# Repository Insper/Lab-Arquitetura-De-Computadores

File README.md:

# Lab-Arquitetura-De-Computadores
Materiais do laboratório de Arquitetura De Computadores Do Insper - Sistemas Embarcados!

## Equipamentos

- Analisador lógico
  - 1x Saleae Logic Pro 16
  - 12x Saleae Logic 8  
- Osciloscópio
  - 3x Tektronix DPO2012B
- Gerador de Sinais
  - 3x Tektronix AFG3021
- Multímetro de Bancada
  - 3x Tektronix DMM4040
- Fonte configurável
  - 6x Tektronix PWS4343

## Kits de desenvolvimento

- microcontrolador
  - 55x SAE70-XPLD
- FPGA SOC
  - 6x DE0-CV
  - 12x Hélio
- FPGA
  - DE5a-NET-DDR4

## Módulos

Os seguinte módulos estão disponíveis no laboratório:

### Atuadores

### Sensores

### Comunicacao

### Interface

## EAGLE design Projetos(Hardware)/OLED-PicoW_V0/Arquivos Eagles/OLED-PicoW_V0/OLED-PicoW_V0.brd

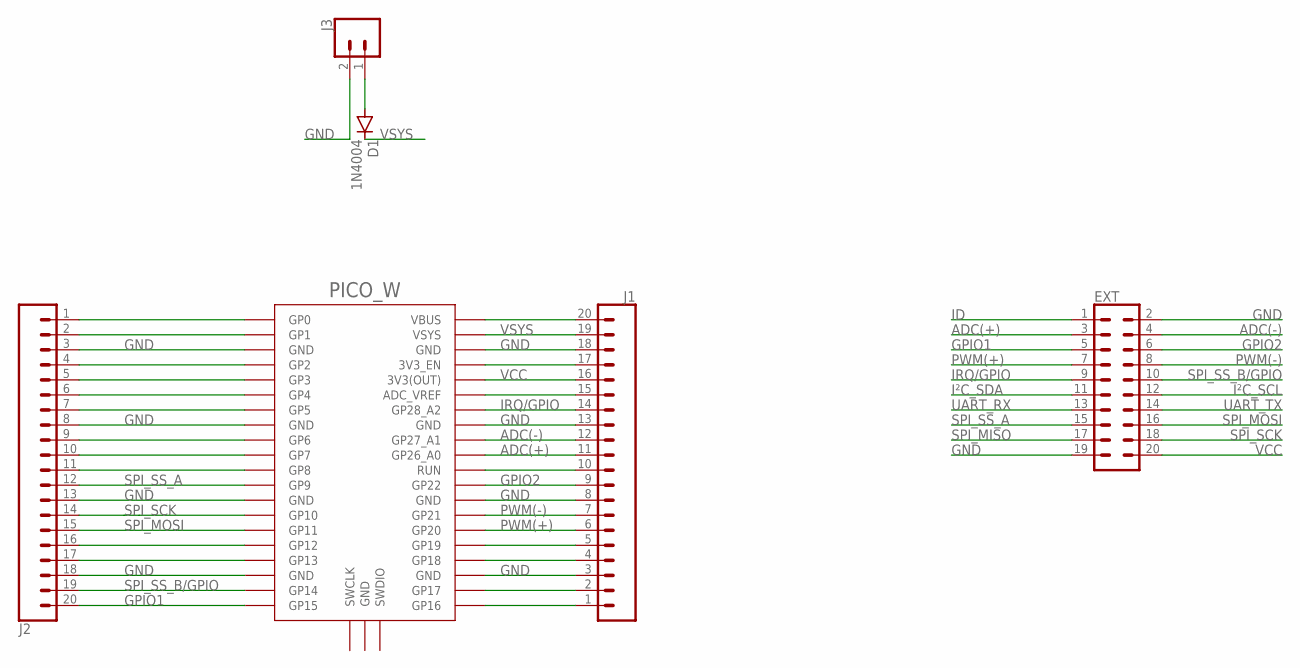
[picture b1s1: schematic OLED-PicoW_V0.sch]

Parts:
D1: 1N4004; DO41-10
EXT: CONN_10X2; 2X10
J1, J2: CONN_20; 1X20
J3: CONN_023.5MM; SCREWTERMINAL-3.5MM-2
PICO_W: RPI_PICO_IG-TH; RPI_PICO_TH

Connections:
ADC(+): EXT.3, J1.11, PICO_W.GP26_A0
ADC(-): EXT.4, J1.12, PICO_W.GP27_A1
GND: EXT.2, EXT.19, J1.3, J1.8, J1.13, J1.18, J2.3, J2.8, J2.13, J2.18, J3.2, PICO_W.AGND (GND), PICO_W.GND@1 (GND), PICO_W.GND@2 (GND), PICO_W.GND@3 (GND), PICO_W.GND@4 (GND), PICO_W.GND@6 (GND), PICO_W.GND@7 (GND), PICO_W.GND@8 (GND)
GPIO1: EXT.5, J2.20, PICO_W.GP15
GPIO2: EXT.6, J1.9, PICO_W.GP22
ID: EXT.1
IRQ/GPIO: EXT.9, J1.14, PICO_W.GP28_A2
I²C_SCL: EXT.12
I²C_SDA: EXT.11
unnamed: J1.20, PICO_W.VBUS
unnamed: J1.5, PICO_W.GP19
unnamed: J1.17, PICO_W.3V3_EN
unnamed: J1.15, PICO_W.ADC_VREF
unnamed: J1.4, PICO_W.GP18
unnamed: J1.10, PICO_W.RUN
unnamed: J1.2, PICO_W.GP17
unnamed: J1.1, PICO_W.GP16
unnamed: J2.1, PICO_W.GP0
unnamed: J2.2, PICO_W.GP1
unnamed: J2.4, PICO_W.GP2
unnamed: J2.5, PICO_W.GP3
unnamed: J2.6, PICO_W.GP4
unnamed: J2.7, PICO_W.GP5
unnamed: J2.9, PICO_W.GP6
unnamed: J2.10, PICO_W.GP7
unnamed: J2.11, PICO_W.GP8
unnamed: J2.16, PICO_W.GP12
unnamed: J2.17, PICO_W.GP13
unnamed: D1.A, J3.1
PWM(+): EXT.7, J1.6, PICO_W.GP20
PWM(-): EXT.8, J1.7, PICO_W.GP21
SPI_MISO: EXT.17
SPI_MOSI: EXT.16, J2.15, PICO_W.GP11
SPI_SCK: EXT.18, J2.14, PICO_W.GP10
SPI_SS_A: EXT.15, J2.12, PICO_W.GP9
SPI_SS_B/GPIO: EXT.10, J2.19, PICO_W.GP14
UART_RX: EXT.13
UART_TX: EXT.14
VCC: EXT.20, J1.16, PICO_W.3V3(OUT)
VSYS: D1.C, J1.19, PICO_W.VSYS

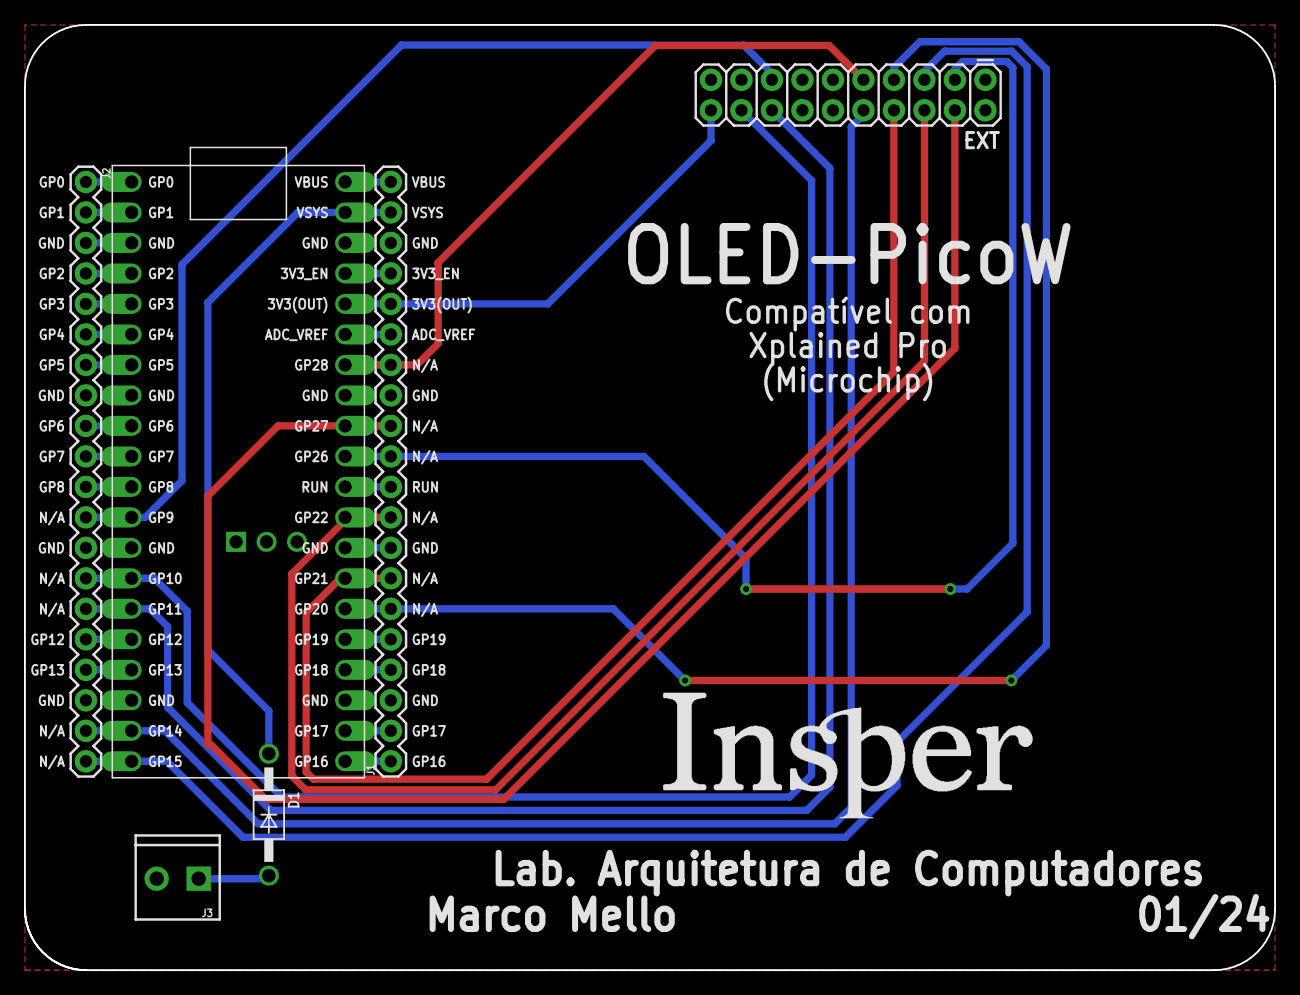
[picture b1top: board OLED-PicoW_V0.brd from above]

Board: 2 copper layers, 104.1 x 78.7 mm, 6 parts (0 on the bottom side), 34 nets.

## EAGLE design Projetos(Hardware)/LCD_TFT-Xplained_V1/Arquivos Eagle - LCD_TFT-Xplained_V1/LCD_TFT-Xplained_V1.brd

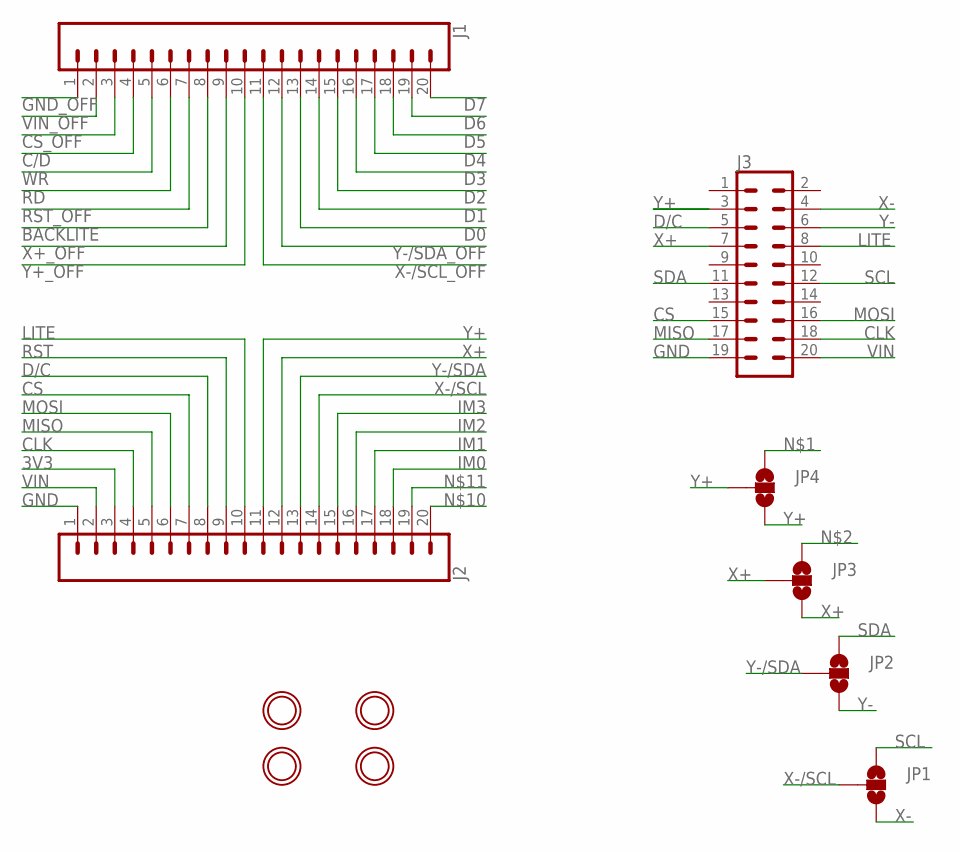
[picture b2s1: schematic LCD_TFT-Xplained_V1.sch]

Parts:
J1, J2: CONN_20NOSILK; 1X20_NOSILK
J3: CONN_10X2; 2X10
JP1, JP2, JP3, JP4: JUMPER-SMT_3_NO_NO-SILK; SMT-JUMPER_3_NO_NO-SILK
U$1, U$2, U$3, U$4: MOUNTINGHOLE3.0THIN; MOUNTINGHOLE_3.0_PLATEDTHIN

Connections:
3V3: J2.3
BACKLITE: J1.8
C/D: J1.4
CLK: J2.4, J3.18
CS: J2.7, J3.15
CS_OFF: J1.3
D0: J1.13
D1: J1.14
D2: J1.15
D3: J1.16
D4: J1.17
D5: J1.18
D6: J1.19
D7: J1.20
D/C: J2.8, J3.5
GND: J2.1, J3.19
GND_OFF: J1.1
IM0: J2.18
IM1: J2.17
IM2: J2.16
IM3: J2.15
LITE: J2.10, J3.8
MISO: J2.5, J3.17
MOSI: J2.6, J3.16
RD: J1.6
RST: J2.9
RST_OFF: J1.7
SCL: J3.12, JP1.1
SDA: J3.11, JP2.1
VIN: J2.2, J3.20
VIN_OFF: J1.2
WR: J1.5
X+: J2.12, J3.7, JP3.2, JP3.3
X+_OFF: J1.9
X-: J3.4, JP1.3
X-/SCL: J2.14, JP1.2
X-/SCL_OFF: J1.11
Y+: J2.11, J3.3, JP4.2, JP4.3
Y+_OFF: J1.10
Y-: J3.6, JP2.3
Y-/SDA: J2.13, JP2.2
Y-/SDA_OFF: J1.12

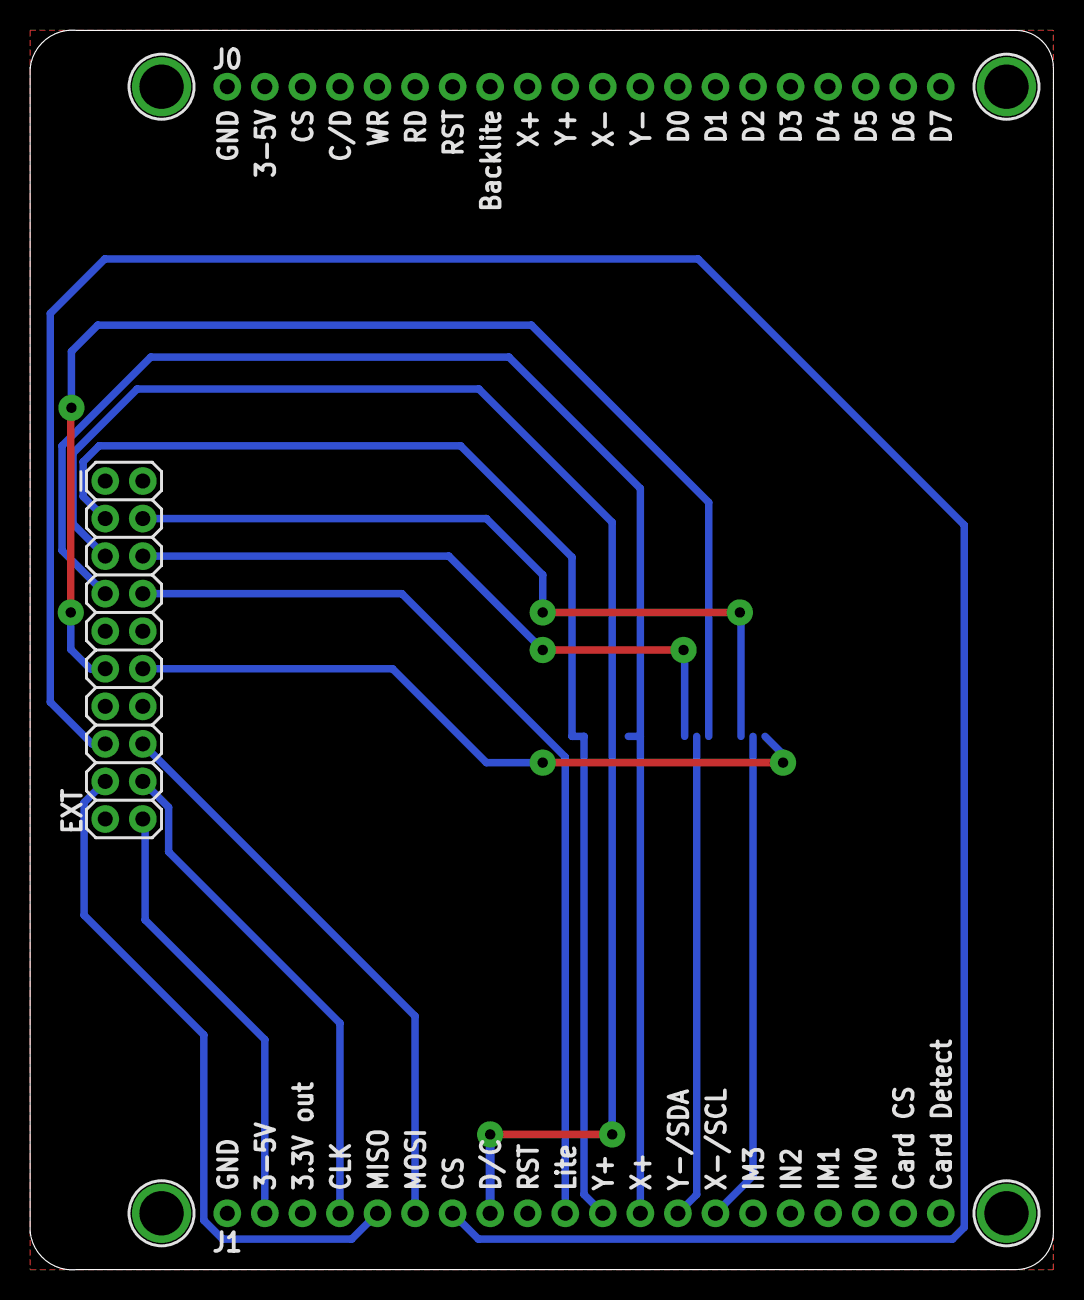
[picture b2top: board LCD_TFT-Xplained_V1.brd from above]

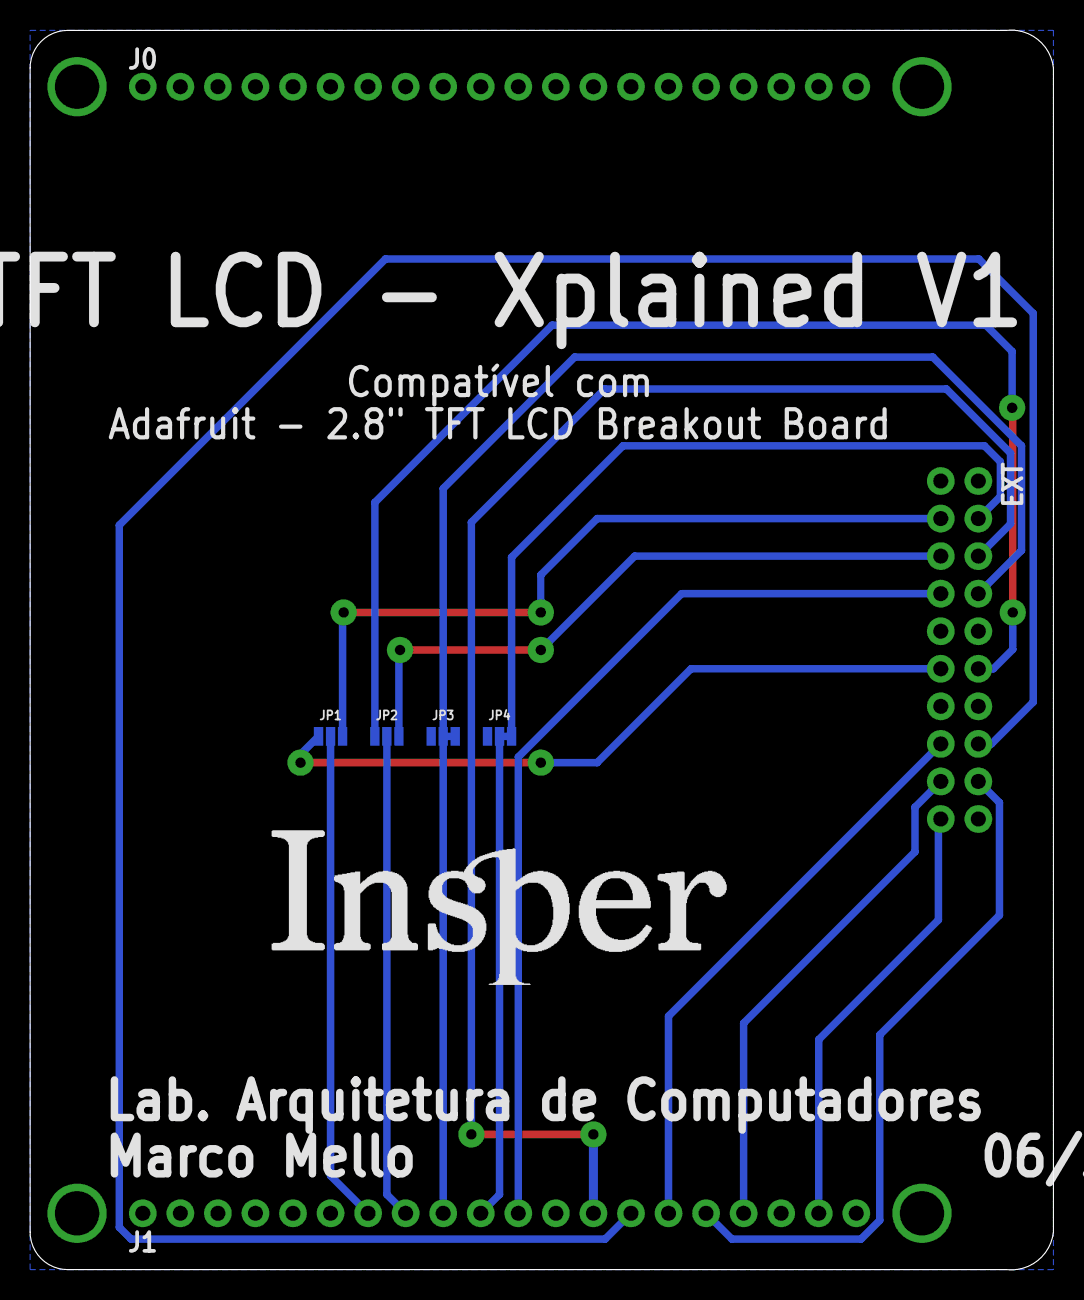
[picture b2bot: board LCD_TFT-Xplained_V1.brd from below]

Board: 2 copper layers, 69.2 x 83.9 mm, 11 parts (4 on the bottom side), 16 nets.

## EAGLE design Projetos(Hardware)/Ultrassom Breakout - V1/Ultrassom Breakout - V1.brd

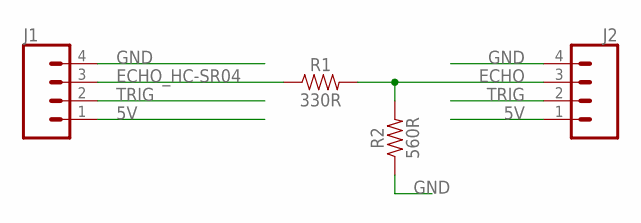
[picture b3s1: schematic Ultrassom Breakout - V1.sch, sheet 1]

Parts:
J1, J2: CONN_041X04_NO_SILK; 1X04_NO_SILK
R1: 330R; AXIAL-0.3-KIT
R2: 560R; AXIAL-0.3-KIT

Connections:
5V: J1.1, J2.1
ECHO: J2.3, R1.P$2 (2), R2.P$2 (2)
ECHO_HC-SR04: J1.3, R1.P$1 (1)
GND: J1.4, J2.4, R2.P$1 (1)
TRIG: J1.2, J2.2

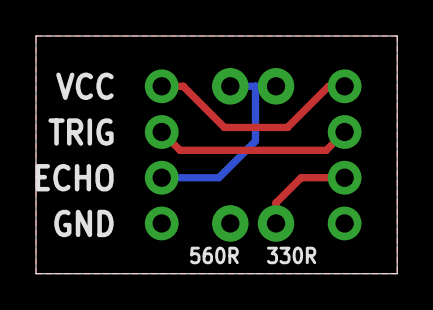
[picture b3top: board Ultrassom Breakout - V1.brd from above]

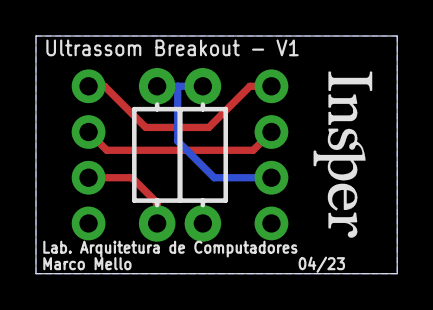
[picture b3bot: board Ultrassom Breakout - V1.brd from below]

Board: 2 copper layers, 20.1 x 13.2 mm, 4 parts (4 on the bottom side), 5 nets.

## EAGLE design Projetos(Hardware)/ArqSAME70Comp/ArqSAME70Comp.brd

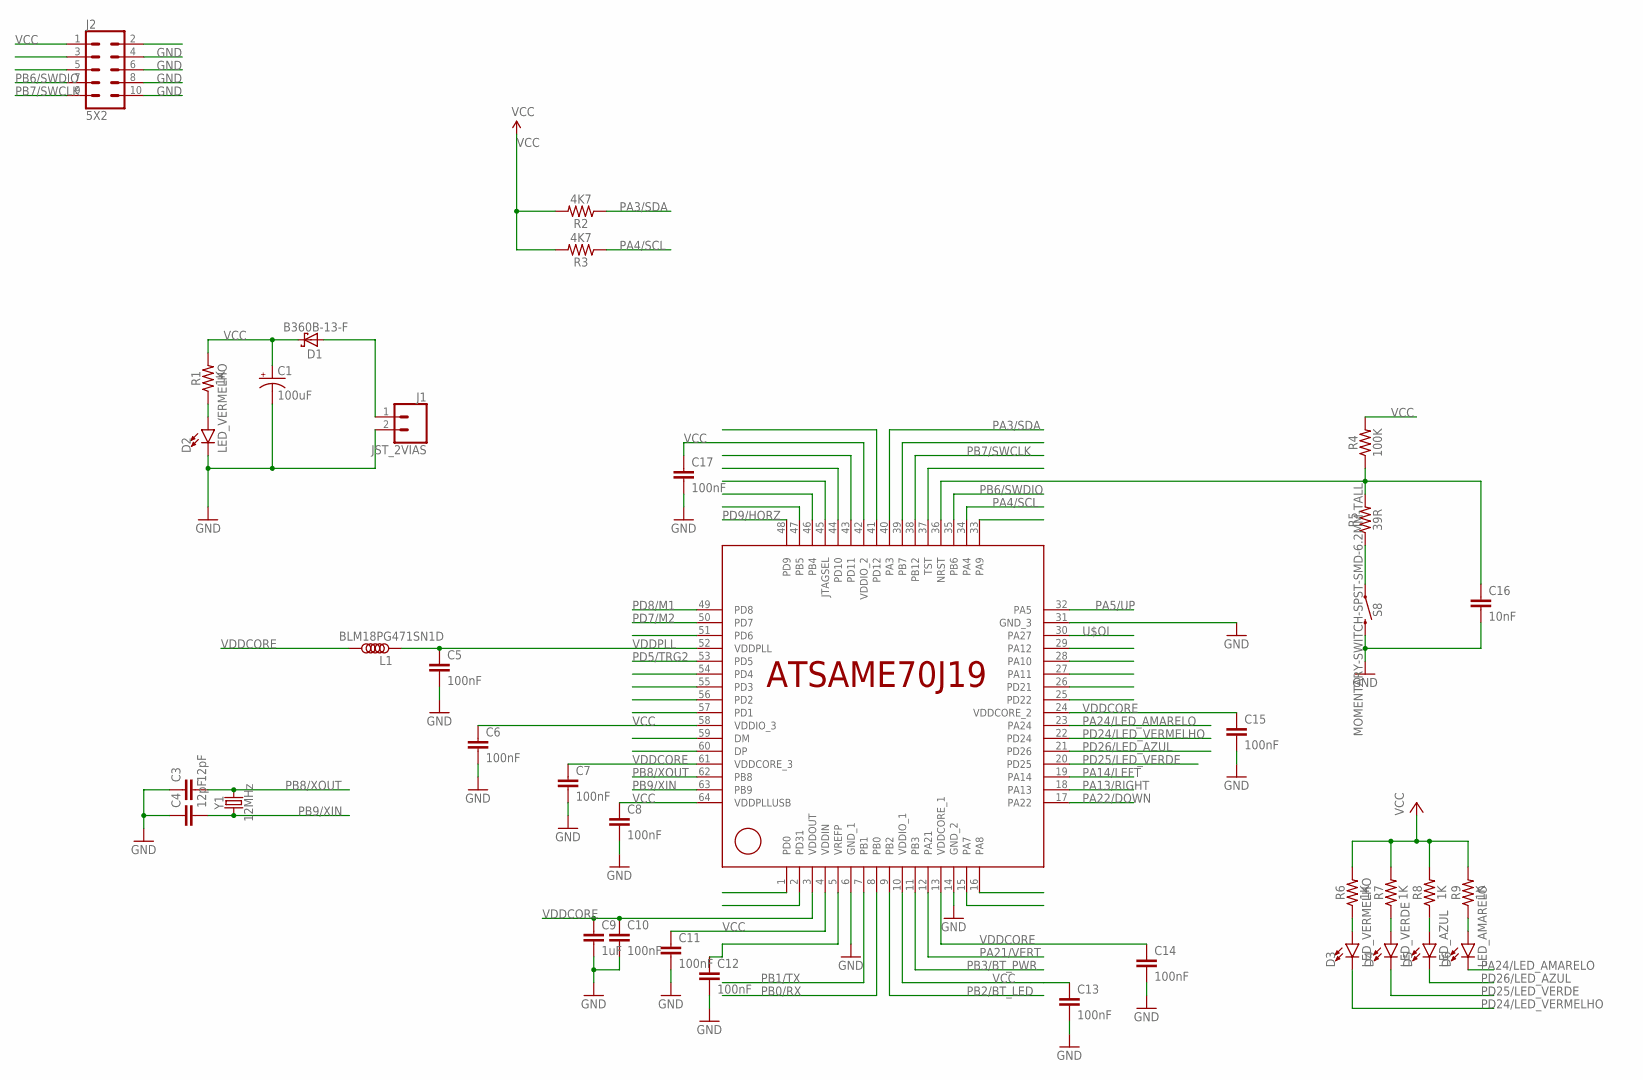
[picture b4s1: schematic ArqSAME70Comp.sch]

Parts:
C1: 100uF; PANASONIC_D
C3, C4: 12pF; 0603
C5, C6, C7, C8, C10, C11, C12, C13, C14, C15, C17: 100nF; C0603K
C9: 1uF; C0603K
C16: 10nF; C0603K
D1: B360B-13-F; DIODE_SMB
D2, D3: LED_VERMELHO; LED-1206
D4: LED_VERDE; LED-1206
D5: LED_AZUL; LED-1206
D6: LED_AMARELO; LED-1206
J1: JST_2VIAS; JST-2-SMD
J2: 5X2; 2X5
L1: BLM18PG471SN1D; PACKAGE_0603
R1, R6, R7, R8, R9: 1K; R0603
R2, R3: 4K7; R0603
R4: 100K; R0603
R5: 39R; R0603
S8: MOMENTARY-SWITCH-SPST-SMD-6.2MM-TALL; TACTILE_SWITCH_SMD_6.2MM_TALL
UC: ATSAME70J19_LQFP64; LQFP64
Y1: 12MHz; CRYSTAL-SMD-5X3.2-4PAD

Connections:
GND: C1.-, C3.1, C4.1, C5.2, C6.2, C7.2, C8.2, C9.2, C10.2, C11.2, C12.2, C13.2, C14.2, C15.2, C16.2, C17.2, D2.C, J1.2 (1), J2.4, J2.6, J2.8, J2.10, S8.B2 (2), UC.6 (GND_1), UC.14 (GND_2), UC.31 (GND_3)
unnamed: D1.A (C), J1.1 (2)
unnamed: D2.A, R1.1
unnamed: R5.1, S8.A2 (1)
unnamed: C12.1, UC.5 (VREFP)
unnamed: D3.A, R6.1
unnamed: D4.A, R7.1
unnamed: D5.A, R8.1
unnamed: D6.A, R9.1
unnamed: C16.1, R4.1, R5.2, UC.36 (NRST)
PA3/SDA: R2.1, UC.40 (PA3)
PA4/SCL: R3.1, UC.34 (PA4)
PA5/UP: UC.32 (PA5)
PA13/RIGHT: UC.18 (PA13)
PA14/LEFT: UC.19 (PA14)
PA21/VERT: UC.12 (PA21)
PA22/DOWN: UC.17 (PA22)
PA24/LED_AMARELO: D6.C, UC.23 (PA24)
PB0/RX: UC.8 (PB0)
PB1/TX: UC.7 (PB1)
PB2/BT_LED: UC.9 (PB2)
PB3/BT_PWR: UC.11 (PB3)
PB6/SWDIO: J2.7, UC.35 (PB6)
PB7/SWCLK: J2.9, UC.39 (PB7)
PB8/XOUT: C3.2, UC.62 (PB8), Y1.3 (2)
PB9/XIN: C4.2, UC.63 (PB9), Y1.1
PD5/TRG2: UC.53 (PD5)
PD7/M2: UC.50 (PD7)
PD8/M1: UC.49 (PD8)
PD9/HORZ: UC.48 (PD9)
PD24/LED_VERMELHO: D3.C, UC.22 (PD24)
PD25/LED_VERDE: D4.C, UC.20 (PD25)
PD26/LED_AZUL: D5.C, UC.21 (PD26)
U$OI: UC.30 (PA27)
VCC: C1.+, C6.1, C8.1, C11.1, C13.1, C17.1, D1.C (A), J2.1, R1.2, R2.2, R3.2, R4.2, R6.2, R7.2, R8.2, R9.2, UC.4 (VDDIN), UC.10 (VDDIO_1), UC.42 (VDDIO_2), UC.58 (VDDIO_3), UC.64 (VDDPLLUSB)
VDDCORE: C7.1, C9.1, C10.1, C14.1, C15.1, L1.2, UC.3 (VDDOUT), UC.13 (VDDCORE_1), UC.24 (VDDCORE_2), UC.61 (VDDCORE_3)
VDDPLL: C5.1, L1.1, UC.52 (VDDPLL)

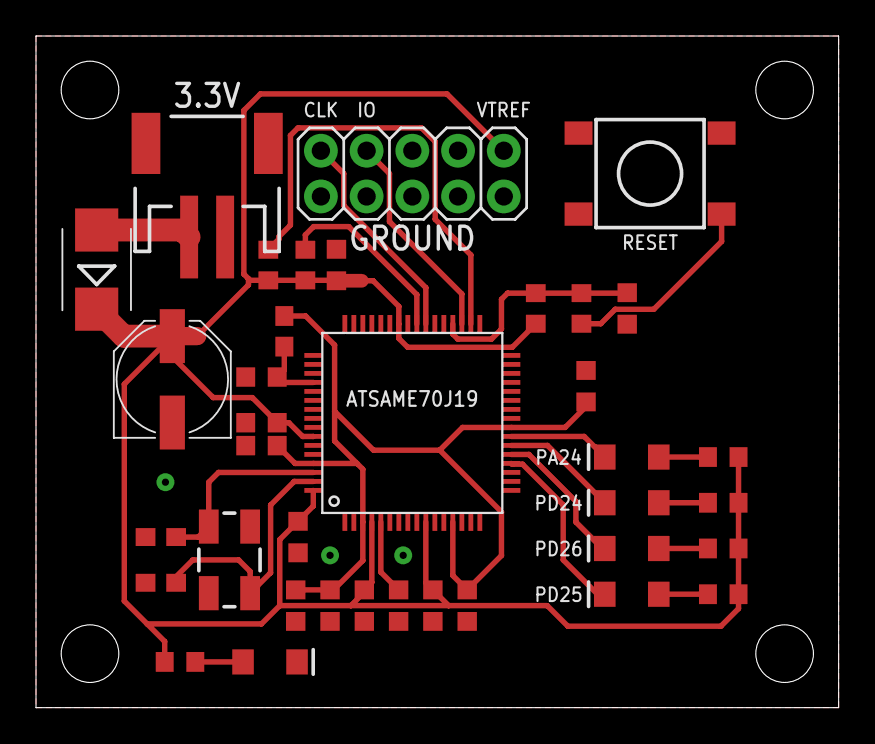
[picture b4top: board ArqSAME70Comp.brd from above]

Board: 2 copper layers, 44.6 x 37.3 mm, 37 parts (0 on the bottom side), 23 nets.

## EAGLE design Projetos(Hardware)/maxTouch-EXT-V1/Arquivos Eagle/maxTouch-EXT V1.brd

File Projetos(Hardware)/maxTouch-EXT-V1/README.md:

# maxTouch-EXT-V1

Shield para liberar o EXT1 e utilizar o maXTouch XPlained

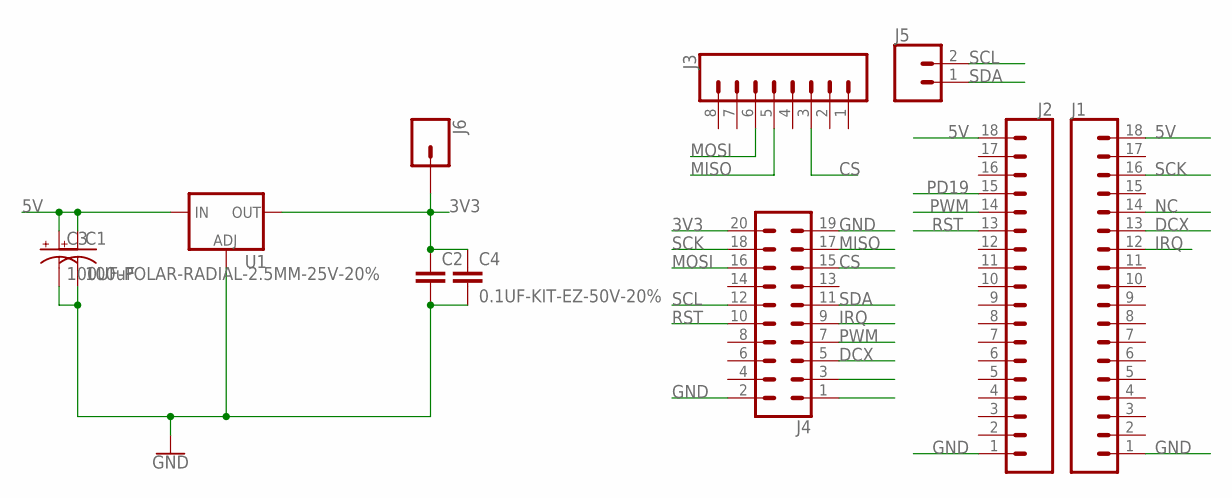
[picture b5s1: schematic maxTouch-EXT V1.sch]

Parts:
C1: 100uF; NIC_10X10.5_CAP
C2: 10uF; 0805
C3: 100UF-POLAR-RADIAL-2.5MM-25V-20%; CPOL-RADIAL-2.5MM-6.5MM
C4: 0.1UF-KIT-EZ-50V-20%; CAP-PTH-SMALL-KIT
J1, J2: CONN_18SILK; 1X18
J3: CONN_08"; 1X08
J4: CONN_10X2; 2X10
J5: CONN_02; 1X02
J6: CONN_01; 1X01
U1: V_REG_LM1117SOT223; SOT223

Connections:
3V3: C2.1, C4.1, J4.20, J6.1, U1.2 (OUT), U1.4 (OUT)
5V: C1.+, C3.1 (+), J1.18, J2.18, U1.3 (IN)
CS: J3.3, J4.15
DCX: J1.13, J4.5
GND: C1.-, C2.2, C3.2 (-), C4.2, J1.1, J2.1, J4.2, J4.19, U1.1 (ADJ)
IRQ: J1.12, J4.9
MISO: J3.5, J4.17
MOSI: J3.6, J4.16
NC: J1.14
PD19: J2.15
PWM: J2.14, J4.7
RST: J2.13, J4.10
SCK: J1.16, J4.18
SCL: J4.12, J5.2
SDA: J4.11, J5.1

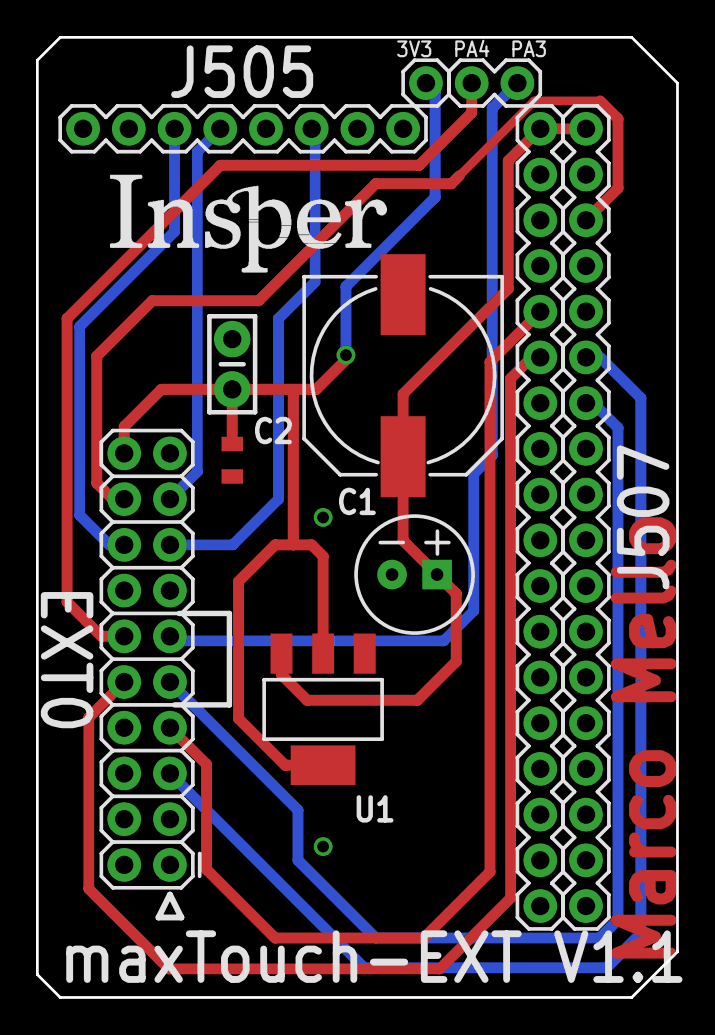
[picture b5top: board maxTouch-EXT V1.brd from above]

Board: 2 copper layers, 35.6 x 53.3 mm, 11 parts (0 on the bottom side), 13 nets.

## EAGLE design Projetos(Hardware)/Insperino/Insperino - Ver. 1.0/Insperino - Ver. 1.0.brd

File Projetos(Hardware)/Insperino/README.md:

# Insperino
Insperino - Arduino Compatível

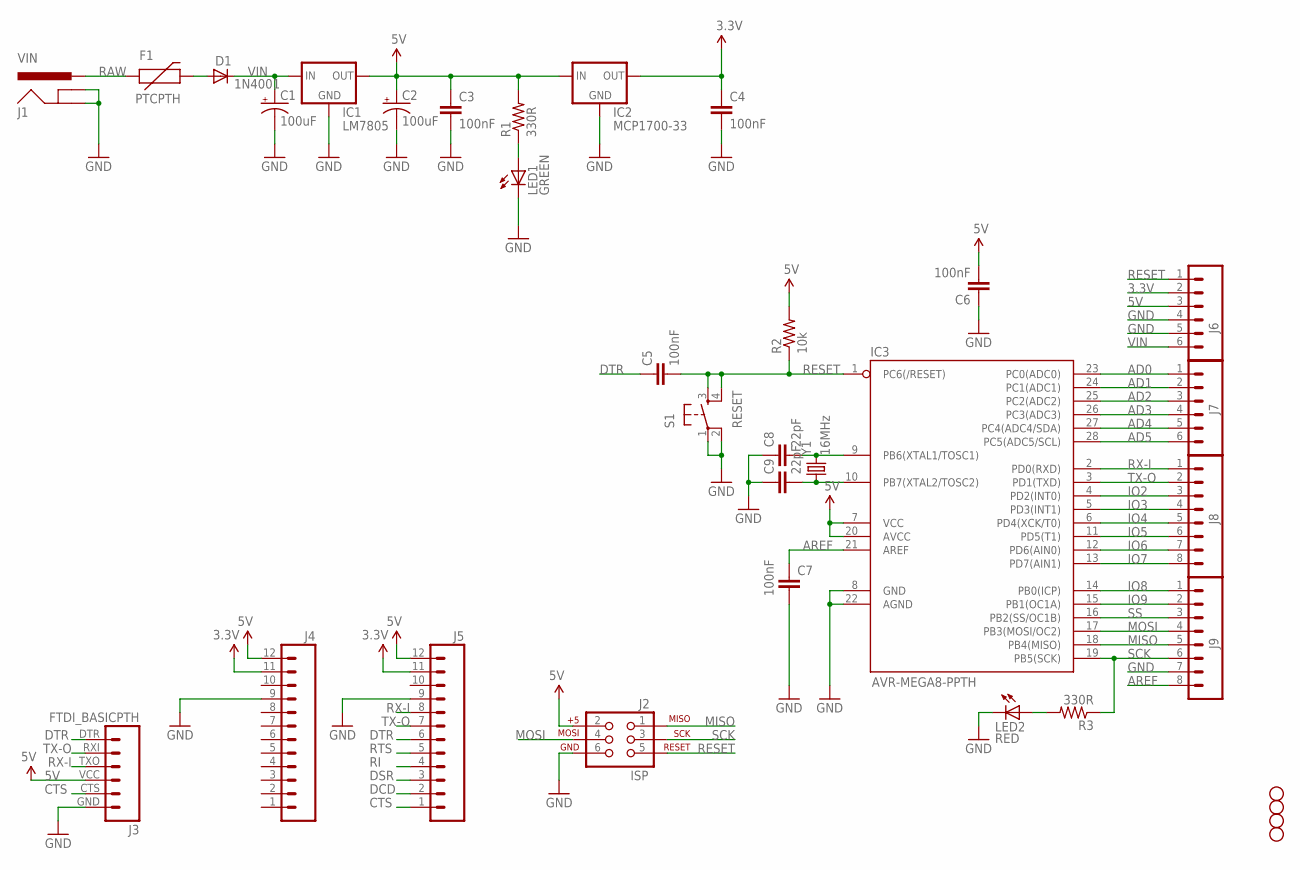
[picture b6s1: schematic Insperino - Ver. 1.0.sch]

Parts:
C1, C2: 100uF; CPOL-RADIAL-100UF-25V
C3, C4, C5, C6, C7: 100nF; CAP-PTH-SMALL2
C8, C9: 22pF; CAP-PTH-SMALL2
D1: 1N4001; DIODE-1N4001
F1: PTCPTH; PTC
IC1: LM7805; TO-220-ALT
IC2: MCP1700-33; TO-92
IC3: AVR-MEGA8-PPTH; DIL28-3
J1: VIN; POWER_JACK_PTH_LOCK
J2: ISP; 2X3
J3: FTDI_BASICPTH; FTDI_BASIC
J4, J5: M12PTH; 1X12
J6, J7: M06SIP; 1X06
J8, J9: M081X08; 1X08
JP3, JP4, JP5, JP6: STAND-OFF
LED1: GREEN; LED5MM
LED2: RED; LED5MM
R1, R3: 330R; AXIAL-0.3
R2: 10k; AXIAL-0.3
S1: RESET; TACTILE-PTH
Y1: 16MHz; HC49US

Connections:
3.3V: C4.1, IC2.3 (OUT), J4.11, J5.11, J6.2
5V: C2.1 (+), C3.1, C6.2, IC1.OUT, IC2.2 (IN), IC3.7 (VCC), IC3.20 (AVCC), J2.2, J3.VCC (4), J4.12, J5.12, J6.3, R1.P$2 (2), R2.P$2 (2)
AD0: IC3.23 (PC0(ADC0)), J7.1
AD1: IC3.24 (PC1(ADC1)), J7.2
AD2: IC3.25 (PC2(ADC2)), J7.3
AD3: IC3.26 (PC3(ADC3)), J7.4
AD4: IC3.27 (PC4(ADC4/SDA)), J7.5
AD5: IC3.28 (PC5(ADC5/SCL)), J7.6
AREF: C7.1, IC3.21 (AREF), J9.8
CTS: J3.CTS (5), J5.1
DCD: J5.2
DSR: J5.3
DTR: C5.1, J3.DTR (1), J5.6
GND: C1.2 (-), C2.2 (-), C3.2, C4.2, C6.1, C7.2, C8.1, C9.1, IC1.GND, IC2.1 (GND), IC3.8 (GND), IC3.22 (AGND), J1.GND, J1.GNDBREAK, J2.6, J3.GND (6), J4.9, J5.9, J6.4, J6.5, J9.7, LED1.K (C), LED2.K (C), S1.1, S1.2
IO2: IC3.4 (PD2(INT0)), J8.3
IO3: IC3.5 (PD3(INT1)), J8.4
IO4: IC3.6 (PD4(XCK/T0)), J8.5
IO5: IC3.11 (PD5(T1)), J8.6
IO6: IC3.12 (PD6(AIN0)), J8.7
IO7: IC3.13 (PD7(AIN1)), J8.8
IO8: IC3.14 (PB0(ICP)), J9.1
IO9: IC3.15 (PB1(OC1A)), J9.2
MISO: IC3.18 (PB4(MISO)), J2.1, J9.5
MOSI: IC3.17 (PB3(MOSI/OC2)), J2.4, J9.4
unnamed: LED2.A, R3.P$2 (2)
unnamed: LED1.A, R1.P$1 (1)
unnamed: C8.2, IC3.9 (PB6(XTAL1/TOSC1)), Y1.2
unnamed: C9.2, IC3.10 (PB7(XTAL2/TOSC2)), Y1.1
unnamed: D1.A, F1.P$2 (2)
RAW: F1.P$1 (1), J1.PWR
RESET: C5.2, IC3.1 (PC6(/RESET)), J2.5, J6.1, R2.P$1 (1), S1.3, S1.4
RI: J5.4
RTS: J5.5
RX-I: IC3.2 (PD0(RXD)), J3.TXO (3), J5.8, J8.1
SCK: IC3.19 (PB5(SCK)), J2.3, J9.6, R3.P$1 (1)
SS: IC3.16 (PB2(SS/OC1B)), J9.3
TX-O: IC3.3 (PD1(TXD)), J3.RXI (2), J5.7, J8.2
VIN: C1.1 (+), D1.C, IC1.IN, J6.6

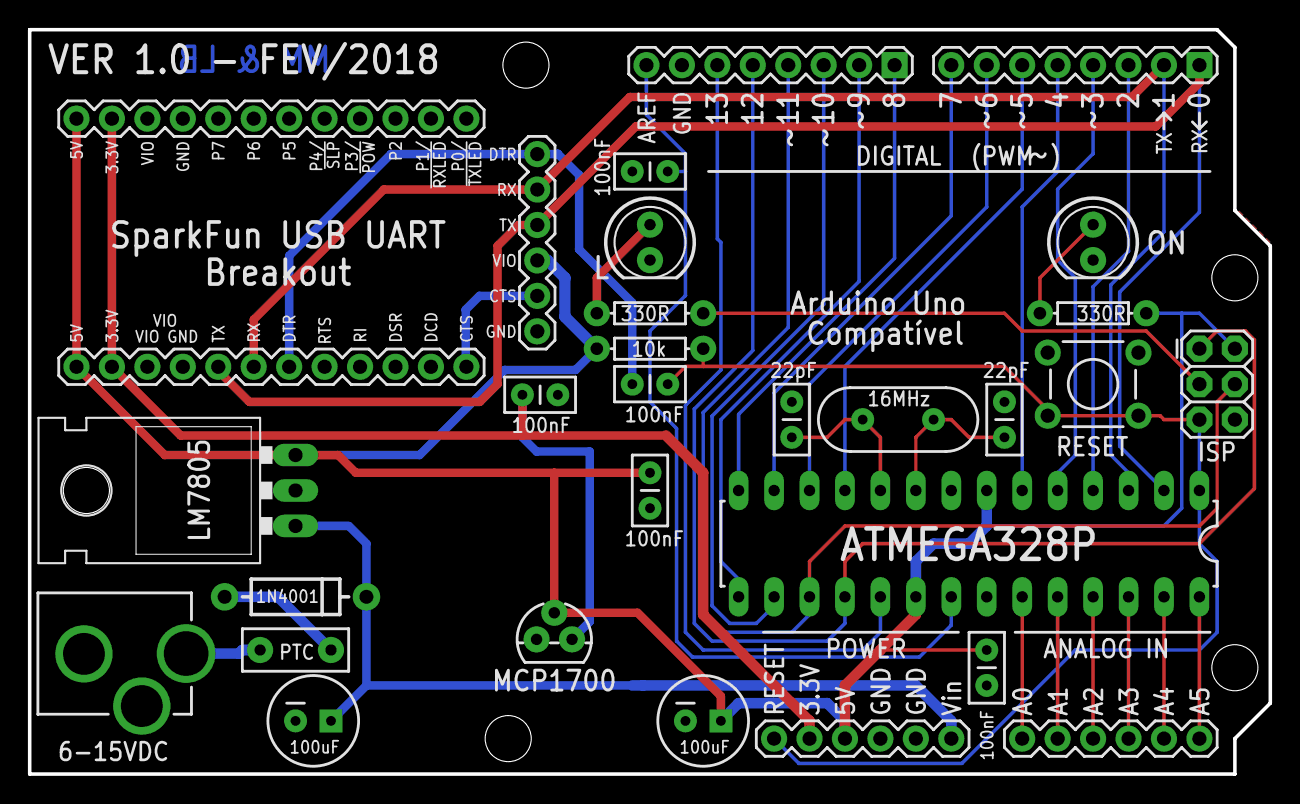
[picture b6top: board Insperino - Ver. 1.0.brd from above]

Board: 2 copper layers, 88.9 x 53.3 mm, 34 parts (0 on the bottom side), 34 nets.

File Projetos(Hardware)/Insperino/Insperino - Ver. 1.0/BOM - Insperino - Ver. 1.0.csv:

Item;Valor;Componentes;Link 1
Capacitor Eletrolítico;100uF/25V;C1;http://proesi.com.br/capacitor-eletrolitico-100uf-25v-105.html
Capacitor Eletrolítico;100uF/25V;C2;http://proesi.com.br/capacitor-eletrolitico-100uf-25v-105.html
Capacitor Cerâmico;100nF/50V;C3;http://proesi.com.br/capacitor-multicamada-100n-50v.html
Capacitor Cerâmico;100nF/50V;C4;http://proesi.com.br/capacitor-multicamada-100n-50v.html
Capacitor Cerâmico;100nF/50V;C5;http://proesi.com.br/capacitor-multicamada-100n-50v.html
Capacitor Cerâmico;100nF/50V;C6;http://proesi.com.br/capacitor-multicamada-100n-50v.html
Capacitor Cerâmico;100nF/50V;C7;http://proesi.com.br/capacitor-multicamada-100n-50v.html
Capacitor Cerâmico;22pF/100V;C8;http://proesi.com.br/catalog/product/view/id/8100/s/capacito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
Capacitor Cerâmico;22pF/100V;C9;http://proesi.com.br/catalog/product/view/id/8100/s/capacito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
Diodo;1N4001;D1;http://proesi.com.br/1n4004-diodo.html
Fusível;PTC RXE030 - 300mA/72V;F1;http://loja.multcomercial.com.br/fusivel-resetavel-rxef030-p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
Regulador de Tensão;LM7805;IC1;http://proesi.com.br/lm7805-circuito-integrado-to-220-compon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
Regulador de Tensão;MCP1700-33;IC2;https://br.mouser.com/ProductDetail/Microchip-Technology/MCP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
Microcontrolador;ATMEGA328P-PU;IC3;https://br.mouser.com/ProductDetail/Microchip-Technology-Atm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
Conector Fêmea Jack-P4;Jack P4;J1;http://proesi.com.br/jack-dc-005-j4-p4-dc-femea-2-1mm-p-sold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
Barra de Pinos;2x3 Pinos;J2;http://proesi.com.br/barra-de-pinos-dupla-2x40x11-2-180.html
Barra de Pinos;6 Pinos;J3;http://proesi.com.br/barra-de-pinos-1x40x11-2-180.html
Barra de Pinos;12 Pinos;J4;http://proesi.com.br/barra-de-pinos-1x40x11-2-180.html
Barra de Pinos;12 Pinos;J5;http://proesi.com.br/barra-de-pinos-1x40x11-2-180.html
Headers Arduino;6 Pinos;J6;https://www.usinainfo.com.br/barras-de-pinos/barra-de-6-pino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
Headers Arduino;6 Pinos;J7;https://www.usinainfo.com.br/barras-de-pinos/barra-de-6-pino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
Headers Arduino;8 Pinos;J8;https://www.usinainfo.com.br/barras-de-pinos/barra-de-8-pino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
Headers Arduino;8 Pinos;J9;https://www.usinainfo.com.br/barras-de-pinos/barra-de-8-pino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
LED 5mm;Verde;LED1;http://proesi.com.br/led-difuso-5mm-verde.html
LED 5mm;Vermelho;LED2;http://proesi.com.br/led-difuso-5mm-vermelho.html
Resistor 1/4W;330R;R1;http://proesi.com.br/resistor-carbono-cr25-1-4w-330r.html
Resistor 1/4W;10k;R2;http://proesi.com.br/resistor-carbono-cr25-1-4w-10k.html
Resistor 1/4W;330R;R3;http://proesi.com.br/resistor-carbono-cr25-1-4w-330r.html
Chave Táctil;6x6x5;S1;http://proesi.com.br/chave-tactil-kfc-a06-6x6x5mm-4t-180.html
Cristal Oscilador;16MHz;Y1;http://proesi.com.br/cristal-oscilador-16mhz-16-000mhz-hc-49s.html
Conversor USB/SERIAL;SparkFun USB UART Serial Breakout - CY7C65213;;https://www.sparkfun.com/products/13830?_ga=2.159165502.5867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
Placa PCB;Griffus;;http://www.griffuspcb.com.br/

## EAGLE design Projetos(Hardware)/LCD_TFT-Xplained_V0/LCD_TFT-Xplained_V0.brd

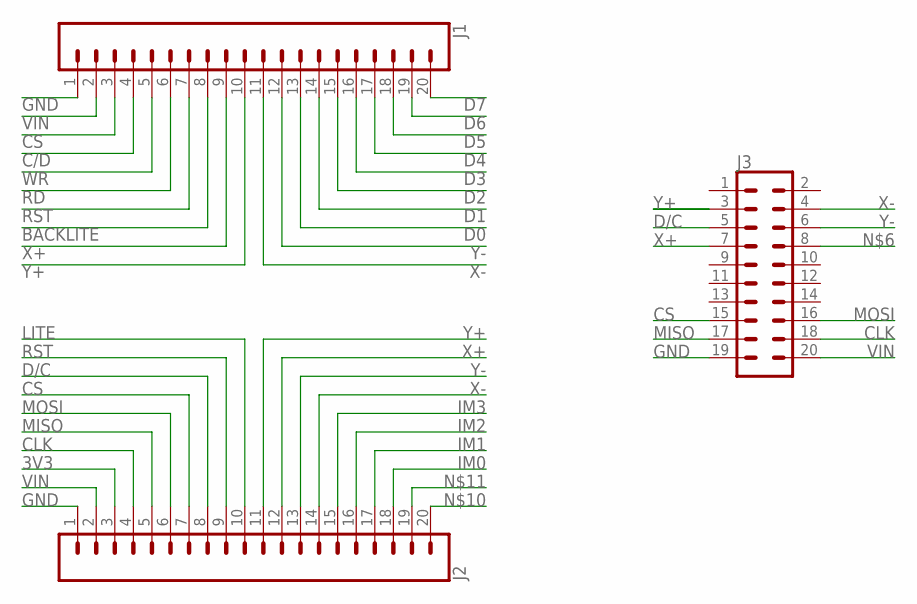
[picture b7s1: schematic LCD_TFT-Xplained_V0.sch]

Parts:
J1, J2: CONN_20NOSILK; 1X20_NOSILK
J3: CONN_10X2; 2X10

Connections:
3V3: J2.3
BACKLITE: J1.8
C/D: J1.4
CLK: J2.4, J3.18
CS: J1.3, J2.7, J3.15
D0: J1.13
D1: J1.14
D2: J1.15
D3: J1.16
D4: J1.17
D5: J1.18
D6: J1.19
D7: J1.20
D/C: J2.8, J3.5
GND: J1.1, J2.1, J3.19
IM0: J2.18
IM1: J2.17
IM2: J2.16
IM3: J2.15
LITE: J2.10
MISO: J2.5, J3.17
MOSI: J2.6, J3.16
RD: J1.6
RST: J1.7, J2.9
VIN: J1.2, J2.2, J3.20
WR: J1.5
X+: J1.9, J2.12, J3.7
X-: J1.11, J2.14, J3.4
Y+: J1.10, J2.11, J3.3
Y-: J1.12, J2.13, J3.6

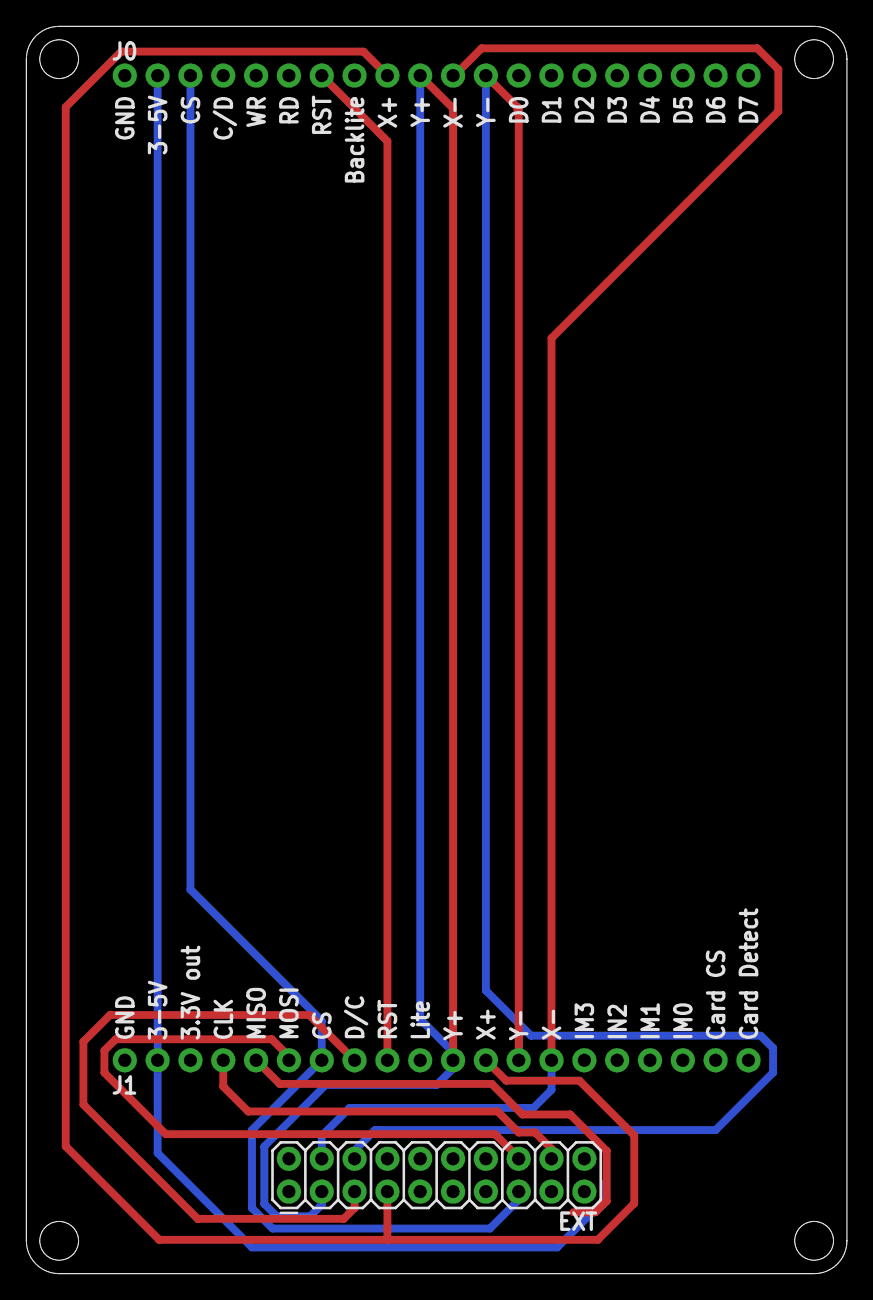
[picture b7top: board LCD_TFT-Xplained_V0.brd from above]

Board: 2 copper layers, 63.5 x 96.5 mm, 3 parts (0 on the bottom side), 12 nets.

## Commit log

2019-02-25 versao 0 do repo
2021-09-23 Criacao do repositorio para projetos de hardware
2021-09-23 Inserido alguns projetos de hardware para o Lab de ArqComp
2021-11-03 Silk em png
2021-11-03 Silk inserido no README
2021-11-18 Correcao de trilha
2022-07-15 adicionado teste placa e bikeSimulator
2022-07-21 cartilhas
2022-08-17 Inserido Panfletos
2023-01-16 nova versao LCD_TFT-Xplained__CAPACITIVO
2023-01-26 Modificando cartilhas para 2023a
2023-03-28 Projeto do Ultrassom Breakout
2023-05-25 Atualizacao LCD tft
2023-06-06 LCD_TFT-Xplained_V1
2024-02-21 Cartilha e Upload do projeto OLED-PicoW
2024-05-07 Cartilhas - MIPS
2024-08-15 cartilha 24b
2025-02-05 Atualizando Cartilha
2025-02-08 atualizado cartilhas 2025a
2026-02-26 cartilha 26a
2026-03-06 cartilhas atualizadas 2026a

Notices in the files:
parts and their libraries:
SparkFun-Connectors: Licensing: Creative Commons ShareAlike 4.0 International - https://creativecommons.org/licenses/by-sa/4.0
